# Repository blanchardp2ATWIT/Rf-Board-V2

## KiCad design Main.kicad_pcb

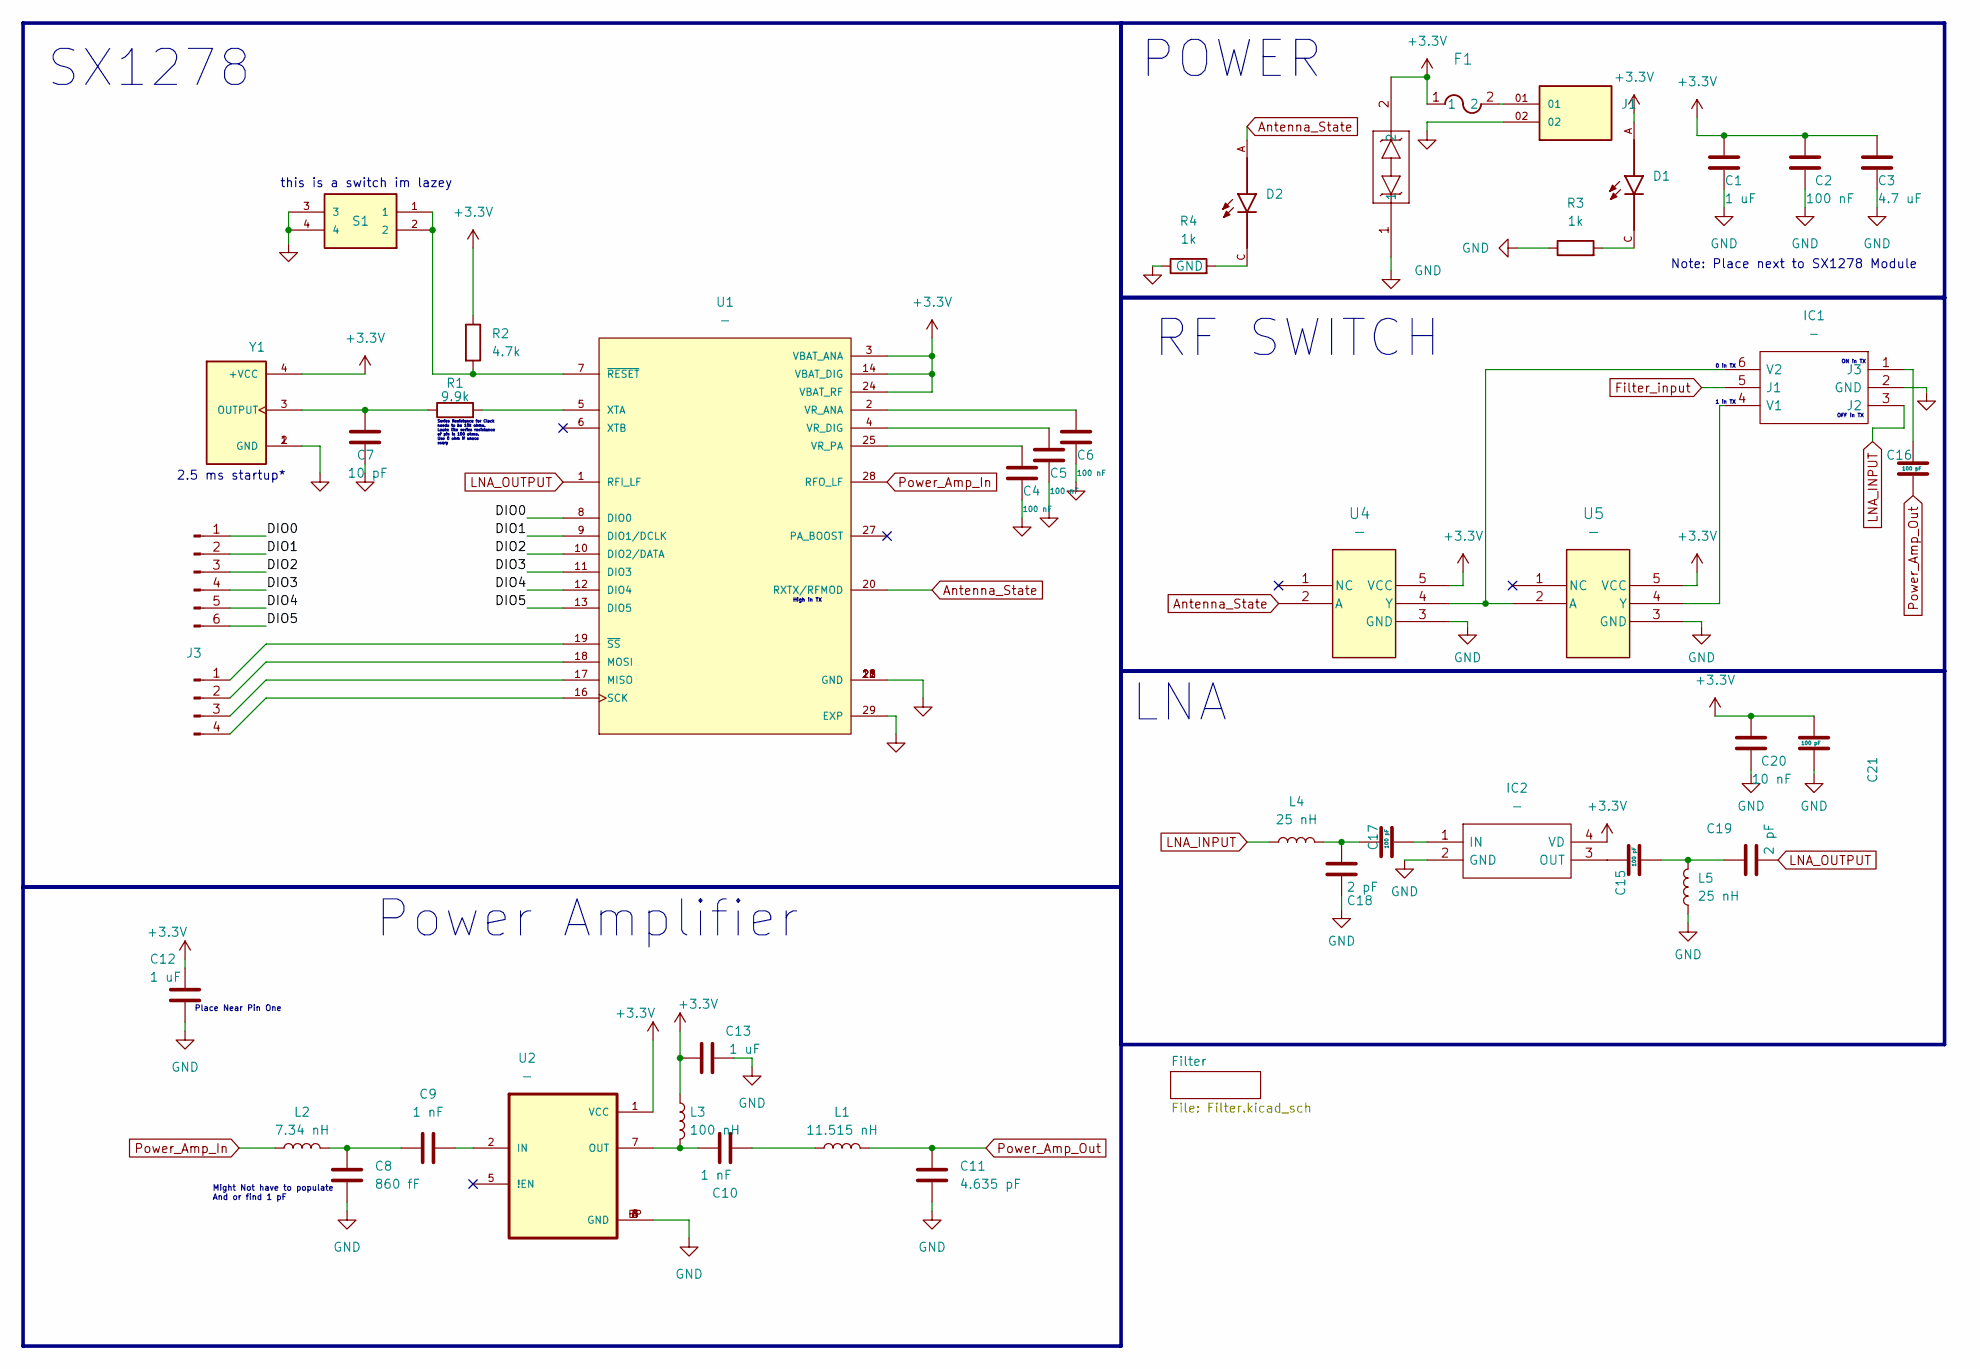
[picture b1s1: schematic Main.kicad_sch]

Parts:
C1, C12, C13: 1 uF; C_0603_1608Metric_Pad1.08x0.95mm_HandSolder; Part Number 885012106010
C2, C4, C5, C6: 100 nF; C_0603_1608Metric_Pad1.08x0.95mm_HandSolder; Part Number 885012206071
C3: 4.7 uF; C_0603_1608Metric_Pad1.08x0.95mm_HandSolder; Part Number 885012106005
C7: 10 pF; C_0603_1608Metric_Pad1.08x0.95mm_HandSolder; Part Number 885012006017
C8: 860 fF; C_0603_1608Metric_Pad1.08x0.95mm_HandSolder; Part Number 885012006087
C9, C10: 1 nF; C_0603_1608Metric_Pad1.08x0.95mm_HandSolder; Part Number 885012006029
C11: 4.635 pF; C_0603_1608Metric_Pad1.08x0.95mm_HandSolder; Part Number 885012006030
C15, C16, C18, C21: 100 pF; C_0603_1608Metric_Pad1.08x0.95mm_HandSolder; Part Number 885012006023
C17, C19: 2 pF; C_0603_1608Metric_Pad1.08x0.95mm_HandSolder; Part Number 885012006047
C20: 10 nF; C_0603_1608Metric_Pad1.08x0.95mm_HandSolder; Part Number 885012006002
CR1: PESD3V3Y1BSFYL; SOD962-2_DSN0603-2_NEX-L
D1, D2: -; LEDC1608X35N; Part Number LTST-C190KRKT
F1: 0ZCJ0025AF2E; 0ZCJ_BEL
IC1: -; SOT65P220X110-6N; Part Number SKYA21001
IC2: -; SOT343; Part Number BGA420H6327XTSA1
J1: -; PHOENIX_1935776; Part Number 1935776
J2: DO NOT PLACE; PinHeader_1x06_P2.54mm_Vertical; Part Number DO NOT PLACE
J3: DO NOT PLACE; PinHeader_1x04_P2.54mm_Vertical; Part Number DO NOT PLACE
L1: 11.515 nH; L_0603_1608Metric_Pad1.05x0.95mm_HandSolder; Part Number 0603DC-11NXJRW
L2: 7.34 nH; L_0603_1608Metric_Pad1.05x0.95mm_HandSolder; Part Number SDWL1608CP7N2JSTF
L3: 100 nH; L_0603_1608Metric_Pad1.05x0.95mm_HandSolder; Part Number 0603DC-11NXJRW
L4, L5: 25 nH; L_0603_1608Metric_Pad1.05x0.95mm_HandSolder; Part Number SDWL1608CP24NJSTF
R1: 9.9k; R_0603_1608Metric_Pad0.98x0.95mm_HandSolder; Part Number ERJ-3GEYJ103V
R2: 4.7k; R_0603_1608Metric_Pad0.98x0.95mm_HandSolder; Part Number ERJ-3GEYJ472V
R3, R4: 1k; R_0603_1608Metric_Pad0.98x0.95mm_HandSolder; Part Number ERJ-3GEYJ102V
S1: -; PTS810SJG250SMTRLFS; Part Number PTS810 SJK 250 SMTR LFS
U1: -; QFN65P600X600X100-29N; Part Number SX1278IMLTRT
U2: -; SON50P200X200X80-9N; Part Number TRF37D73IDSGT
U4, U5: -; DBV5; Part Number SN74AHC1G14DBVR
Y1: 32 MHz; XTAL_ASTX-13-D-32.000MHz-I05-T; Part Number O 30,0-JT22S-B-K-3,3-LF

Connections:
+3.3V: C1.1, C2.1, C3.1, C12.2, C13.2, C20.1, C21.1, CR1.2, D1.A, F1.1, IC2.4 (VD), L3.1, R2.1, U1.3 (VBAT_ANA), U1.14 (VBAT_DIG), U1.24 (VBAT_RF), U2.1 (VCC), U4.5 (VCC), U5.5 (VCC), Y1.4 (+VCC)
/DIO0: J2.1, U1.8 (DIO0)
/DIO1: J2.2, U1.9 (DIO1/DCLK)
/DIO2: J2.3, U1.10 (DIO2/DATA)
/DIO3: J2.4, U1.11 (DIO3)
/DIO4: J2.5, U1.12 (DIO4)
/DIO5: J2.6, U1.13 (DIO5)
Antenna_State: D2.A, U1.20 (RXTX/RFMOD), U4.2 (A)
Filter_input: IC1.5 (J1); also elsewhere on the board
GND: C1.2, C2.2, C3.2, C4.2, C5.2, C6.2, C7.2, C8.2, C11.2, C12.1, C13.1, C17.2, C20.2, C21.2, CR1.1, IC1.2 (GND), IC2.2 (GND), J1.02, L5.1, R3.1, R4.1, S1.3, S1.4, U1.15 (GND), U1.21 (GND), U1.22 (GND), U1.23 (GND), U1.26 (GND), U1.29 (EXP), U2.3 (GND), U2.4 (GND), U2.6 (GND), U2.8 (GND), U2.EP (GND), U4.3 (GND), U5.3 (GND), Y1.1 (GND), Y1.2 (GND); also elsewhere on the board
LNA_INPUT: IC1.3 (J2), L4.1
LNA_OUTPUT: C19.2, U1.1 (RFI_LF)
unnamed: C8.1, C9.1, L2.2
unnamed: C10.2, L1.1
unnamed: C15.1, C19.1, L5.2
unnamed: C17.1, C18.2, L4.2
unnamed: D1.C, R3.2
unnamed: D2.C, R4.2
unnamed: F1.2, J1.01
unnamed: C16.2, IC1.1 (J3)
unnamed: IC1.4 (V1), U5.4 (Y)
unnamed: IC1.6 (V2), U4.4 (Y), U5.2 (A)
unnamed: C18.1, IC2.1 (IN)
unnamed: C15.2, IC2.3 (OUT)
unnamed: J3.1, U1.19 (~SS)
unnamed: J3.2, U1.18 (MOSI)
unnamed: J3.3, U1.17 (MISO)
unnamed: J3.4, U1.16 (SCK)
unnamed: C6.1, U1.2 (VR_ANA)
unnamed: C5.1, U1.4 (VR_DIG)
unnamed: C4.1, U1.25 (VR_PA)
unnamed: R1.2, U1.5 (XTA)
unnamed: R2.2, S1.1, S1.2, U1.7 (~RESET)
unnamed: C9.2, U2.2 (IN)
unnamed: C10.1, L3.2, U2.7 (OUT)
unnamed: C7.1, R1.1, Y1.3 (OUTPUT)
Power_Amp_In: L2.1, U1.28 (RFO_LF)
Power_Amp_Out: C11.1, C16.1, L1.2

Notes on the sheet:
Place Near Pin One
1 in TX
2.5 ms startup*
this is a switch im lazey
Series Resistance for Clock needs to be 10k ohms. Looks like series resistance of pin is 100 ohms. Use 0 ohm if unece ssary
Note: Place next to SX1278 Module
SX1278
ON in TX
POWER
0 in TX
LNA
RF SWITCH
Might Not have to populate And or find 1 pF
High in TX
Power Amplifier
OFF in TX

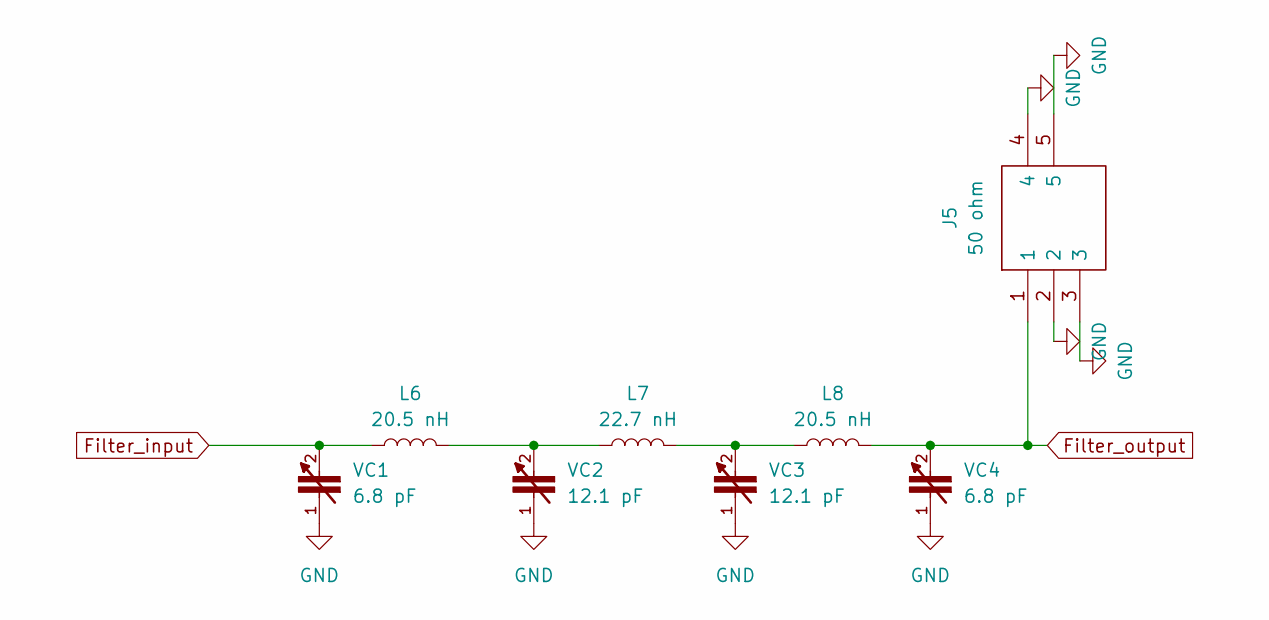
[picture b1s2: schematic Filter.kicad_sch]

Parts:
J5: 50 ohm; 518144002; Part Number 5-1814400-2
L6, L8: 20.5 nH; RESC1608X55N; Part Number 0603DC-20NXJRW
L7: 22.7 nH; RESC1608X55N; Part Number LQW18AS22NJ0CD
VC1, VC4: 6.8 pF; C_0603_1608Metric_Pad1.08x0.95mm_HandSolder; Part Number GCM1885C2A6R8BA16D
VC2, VC3: 12.1 pF; C_0603_1608Metric_Pad1.08x0.95mm_HandSolder; Part Number GCM1885C2A120JA16D

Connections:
Filter_input: L6.1, VC1.2; also elsewhere on the board
Filter_output: J5.1, L8.2, VC4.2
GND: J5.2, J5.3, J5.4, J5.5, VC1.1, VC2.1, VC3.1, VC4.1; also elsewhere on the board
unnamed: L6.2, L7.1, VC2.2
unnamed: L7.2, L8.1, VC3.2

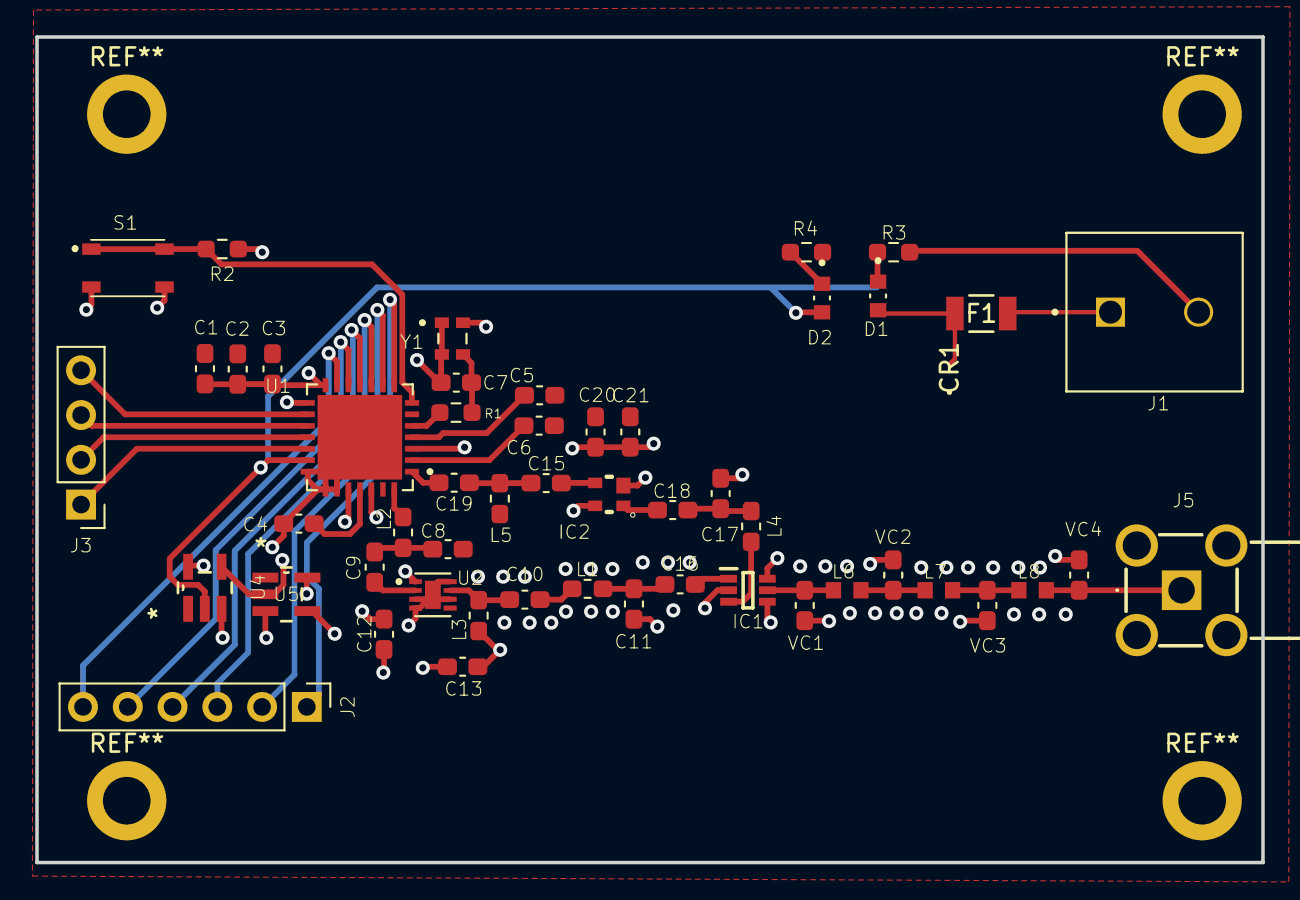
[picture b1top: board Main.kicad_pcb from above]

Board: 4 copper layers, 69.6 x 46.8 mm, 52 parts (0 on the bottom side), 41 nets.

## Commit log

2023-10-21 Started Schem.
2023-10-27 Filter Update
